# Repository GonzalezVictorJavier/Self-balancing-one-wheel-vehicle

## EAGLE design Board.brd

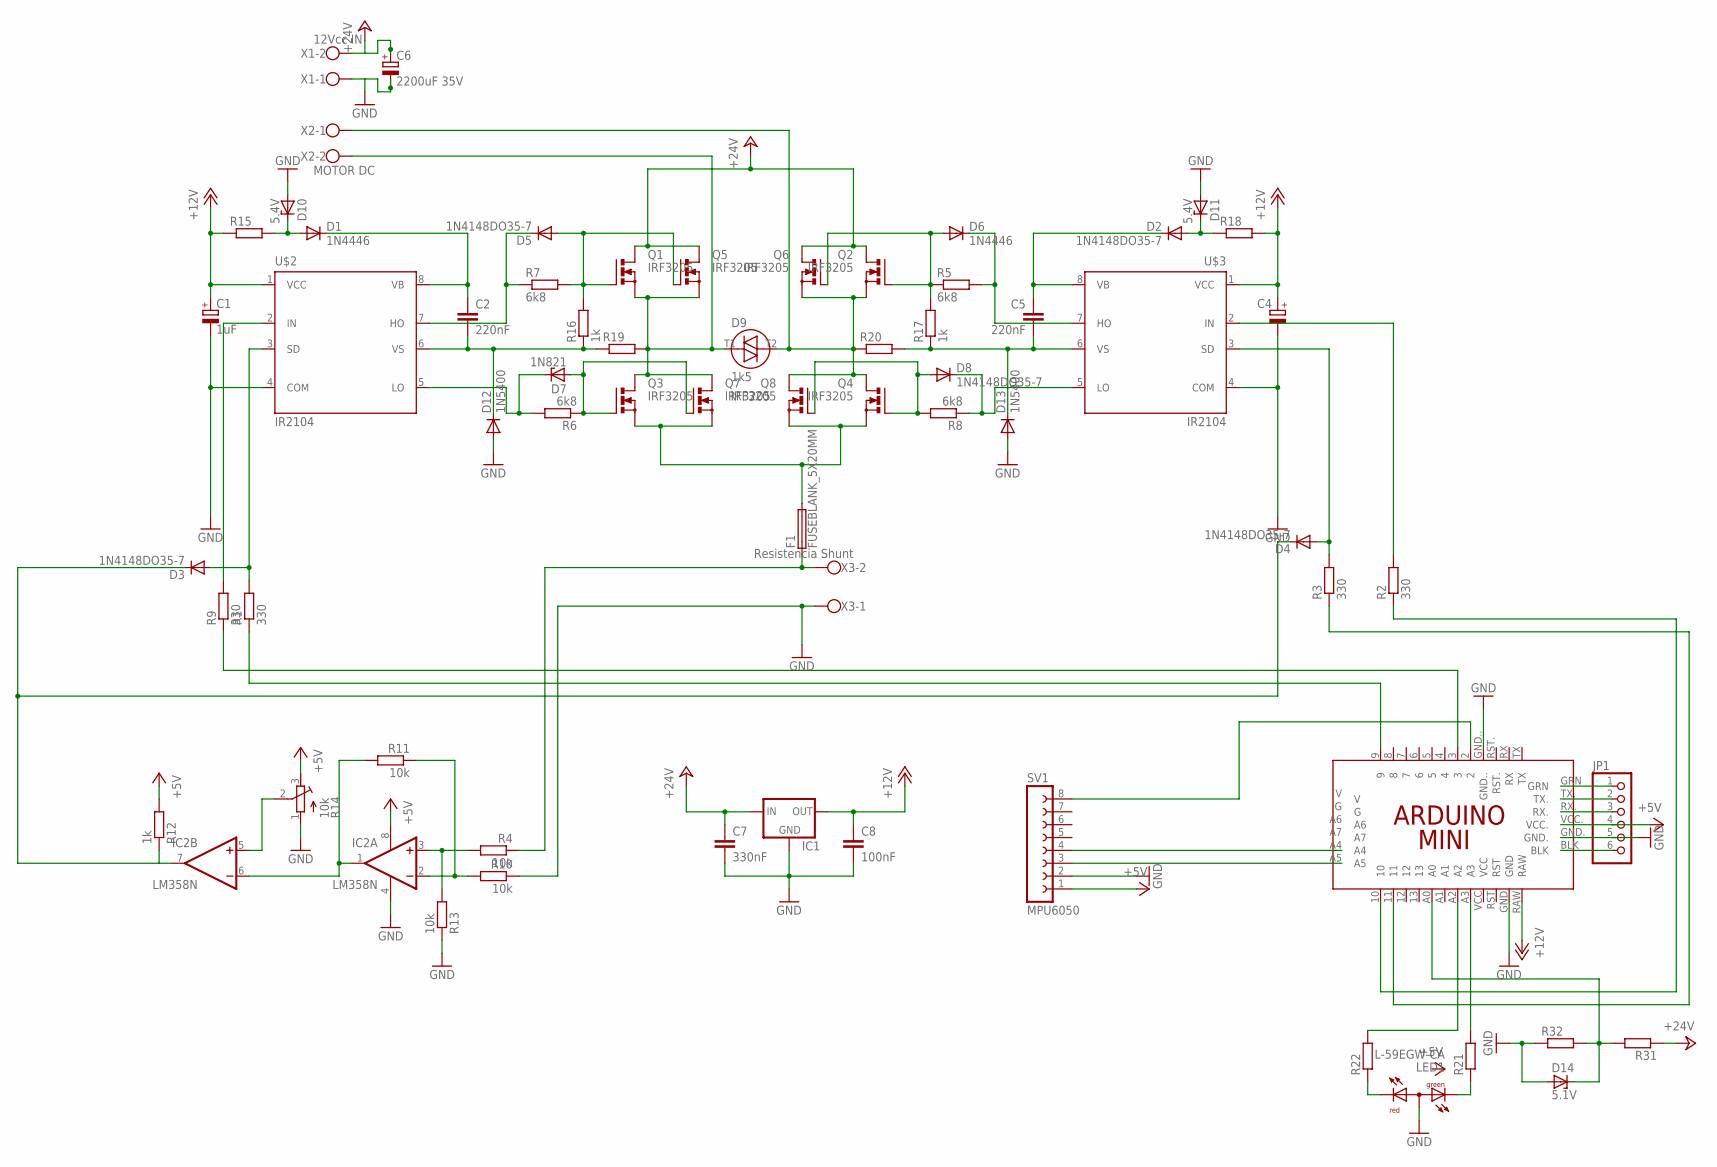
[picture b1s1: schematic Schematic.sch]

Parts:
C1: 1uF; E3,5-8
C2, C5: 220nF; C075-032X103
C4: CPOL-EUE3.5-8; E3,5-8
C6: 2200uF 35V; E5-13
C7: 330nF; C050-024X044
C8: 100nF; C050-024X044
D1, D6: 1N4446; DO35-10
D2, D3, D4, D5, D8: 1N4148DO35-7; DO35-7
D7: 1N821; DO35Z10
D9: 1k5; BR210S
D10, D11: 5.4V; DO34Z7
D12, D13: 1N5400; DO201-15
D14: 5.1V; DO34Z7
F1: FUSEBLANK_5X20MM; FUSE_HOLDER_5X20MM
IC1: 78XXL
IC2: LM358N; DIL08
JP1: PINHD-1X6; 1X06
LED1: L-59EGW-CA
Q1, Q2, Q3, Q4, Q5, Q6, Q7, Q8: IRF3205; TO220BV
R1: 330; 0204/7
R2, R3: 330; 0207/12
R4, R10, R11, R13: 10k; 0204/7
R5: 6k8; 0207/12
R6: 6k8; 0207/15
R7, R8: 6k8; 0204/7
R9: 330; 0207/10
R12: 1k; 0204/7
R14: 10k; RTRIM64W
R15, R18: R-EU_0204/7; 0204/7
R16, R17: 1k; 0207/10
R19, R20: R-EU_0207/15; 0207/15
R21, R22, R31, R32: R-EU_0204/5; 0204/5
SV1: MPU6050; FE08
U$1: ARDUINO_MINI_PRO+AZUL
U$2, U$3: IR2104
X1: 12Vcc IN; W237-102
X2: MOTOR DC; W237-102
X3: Resistencia Shunt; W237-102

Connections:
+5V: IC2.8 (V+), JP1.4, R12.2, R14.3 (E), SV1.1, U$1.VCC.
+12V: C1.+, C4.+, C8.1, IC1.OUT, R15.1, R18.2, U$1.RAW, U$2.1 (VCC), U$3.1 (VCC)
+24V: C6.+, C7.1, IC1.IN, Q1.D, Q2.D, Q5.D, Q6.D, R31.1, X1.2
GND: C1.-, C4.-, C6.-, C7.2, C8.2, D10.A, D11.A, D12.A, D13.A, D14.A, IC1.GND, IC2.4 (V-), JP1.5, LED1.2 (A), R10.1, R13.1, R14.1 (A), R32.1, SV1.2, U$1.GND, U$1.GND., U$1.GND.., U$2.4 (COM), U$3.4 (COM), X1.1, X3.1
unnamed: R9.2, U$2.2 (IN)
unnamed: C2.1, D1.C, U$2.8 (VB)
unnamed: F1.1, R4.1, X3.2
unnamed: D6.A, Q2.G, Q6.G, R5.1, R17.2
unnamed: R2.2, U$3.2 (IN)
unnamed: D4.A, R3.2, U$3.3 (SD)
unnamed: R1.1, U$1.9
unnamed: D3.C, D4.C, IC2.7 (OUT), R12.1
unnamed: D7.A, Q3.G, Q7.G, R6.1
unnamed: R9.1, U$1.3
unnamed: D8.A, Q4.G, Q8.G, R8.2
unnamed: C2.2, D12.C, R16.1, R19.1, U$2.6 (VS)
unnamed: D5.A, Q1.G, Q5.G, R7.2, R16.2
unnamed: SV1.3, U$1.A5
unnamed: LED1.1 (CR), R22.1
unnamed: D1.A, D10.C, R15.2
unnamed: F1.2, Q3.S, Q4.S, Q7.S, Q8.S
unnamed: R2.1, U$1.10
unnamed: C5.1, D2.C, U$3.8 (VB)
unnamed: SV1.4, U$1.A4
unnamed: IC2.1 (OUT), IC2.6 (-IN), R11.2
unnamed: D5.C, R7.1, U$2.7 (HO)
unnamed: D7.C, R6.2, U$2.5 (LO)
unnamed: D8.C, R8.1, U$3.5 (LO)
unnamed: D6.C, R5.2, U$3.7 (HO)
unnamed: IC2.3 (+IN), R4.2, R13.2
unnamed: D3.A, R1.2, U$2.3 (SD)
unnamed: D2.A, D11.C, R18.1
unnamed: LED1.3 (CG), R21.1
unnamed: IC2.2 (-IN), R10.2, R11.1
unnamed: IC2.5 (+IN), R14.2 (S)
unnamed: R3.1, U$1.11
unnamed: D9.T2, Q2.S, Q4.D, Q6.S, Q8.D, R20.1, X2.1
unnamed: D9.T1, Q1.S, Q3.D, Q5.S, Q7.D, R19.2, X2.2
unnamed: C5.2, D13.C, R17.1, R20.2, U$3.6 (VS)
unnamed: SV1.8, U$1.2
unnamed: R21.2, U$1.A3
unnamed: R22.2, U$1.A2
unnamed: JP1.6, U$1.BLK
unnamed: JP1.3, U$1.RX.
unnamed: JP1.2, U$1.TX.
unnamed: JP1.1, U$1.GRN
unnamed: D14.C, R31.2, R32.2, U$1.A0

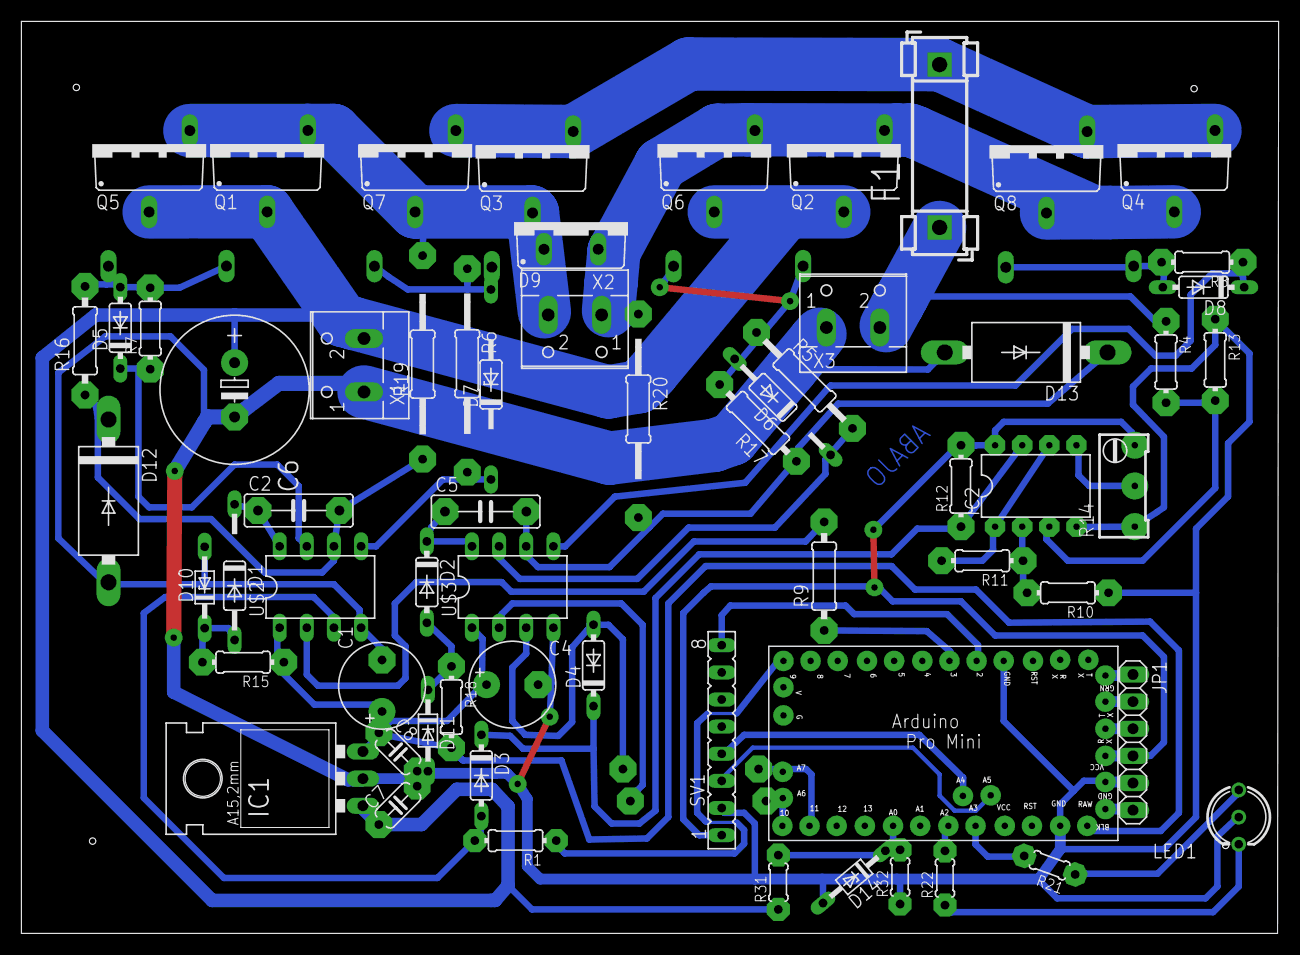
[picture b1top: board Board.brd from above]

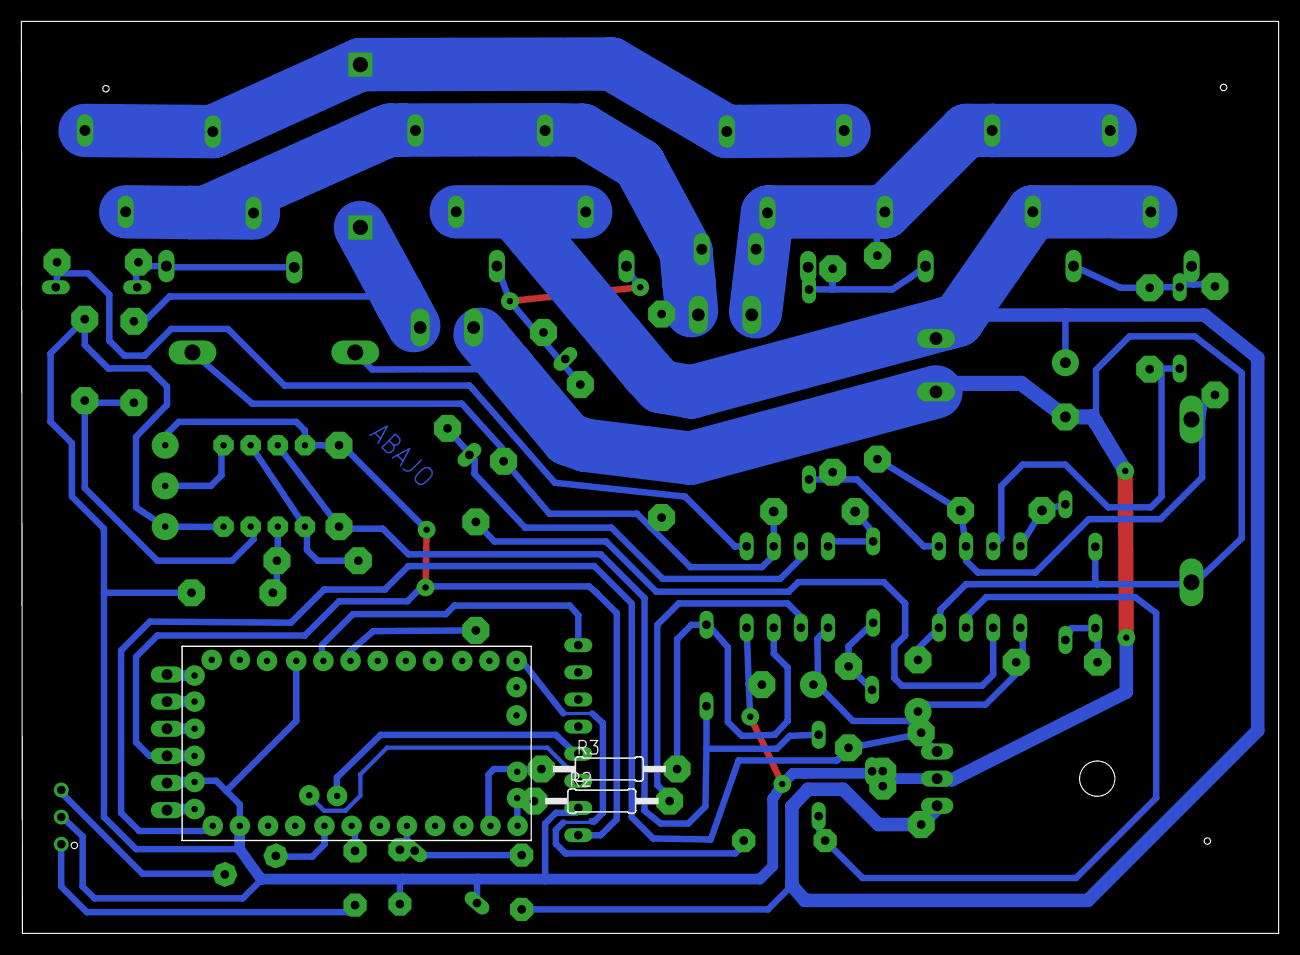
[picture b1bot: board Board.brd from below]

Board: 2 copper layers, 117.6 x 85.2 mm, 65 parts (2 on the bottom side), 47 nets.

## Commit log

2021-12-21 Ver 1
    This is only the board, just for testing of a home-made H bridge to control the motor.
2021-12-21 Ver 2
    Board: A new design using a IC H bridge driver properly calculated for the motor and mosfets.
    Algorithm: An algorithm that use a 3 axis gyro to balance itself.
2021-12-21 Ver 3
    Board: Some adjustments at the design.
    Algorithm: Adjustments too.
2021-12-21 Ver 4
    Board: I made a mistake and the mosfets weren't as robust as the motor require, so i put two in parallel by vertex of the H bridge (8 in total ).
    Algorithm: Some adjustments at parameters.
2021-12-21 Ver 5
    Board: The power consumption is huge, so i needed to make thicker the board contacts. I also included a battery charge sensing.
2021-12-21 Ver 6
    Board: I added some shunt diodes to avoid voltage spikes that could burn out the circuit.
2021-12-21 Ver 7
    Board: Some mixed improvements:
    Algorithm: I needed to invert the X and Y axis.
